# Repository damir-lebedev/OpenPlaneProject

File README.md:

<!-- download:start -->
<p align="center">

</p>
<p align="center"><a href="https://github.com/damir-lebedev/openplane-studio/releases/latest">OpenPlane Studio — настроить, прошить и полететь: самолёт и коптер (в том числе плату из-под Betaflight). Установщик работает без интернета — всё нужное внутри. На Android — настройка и прошивка в поле по кабелю USB-C ⇄ USB-C.</a></p>
<!-- download:end -->

<!-- i18n-bar:start -->
  <p align="center">
     <b>Читать на русском</b>
    &nbsp;·&nbsp;
    <a href="docs/i18n/en/README.md"> Read this in English</a>
    &nbsp;·&nbsp;
    <a href="docs/i18n/zh-CN/README.md"> 阅读中文版</a>
    &nbsp;·&nbsp;
    <a href="docs/i18n/es/README.md"> Lee esto en español</a>
  </p>
  <p align="center">
    <a href="docs/i18n/hi/README.md"> हिन्दी में पढ़ें</a>
    &nbsp;·&nbsp;
    <a href="docs/i18n/ar/README.md"> اقرأ بالعربية</a>
    &nbsp;·&nbsp;
    <a href="docs/i18n/pt-BR/README.md"> Leia em português</a>
    &nbsp;·&nbsp;
    <a href="docs/i18n/fr/README.md"> Lire en français</a>
  </p>
  <p align="center">
    <a href="docs/i18n/de/README.md"> Auf Deutsch lesen</a>
    &nbsp;·&nbsp;
    <a href="docs/i18n/ja/README.md"> 日本語で読む</a>
    &nbsp;·&nbsp;
    <a href="docs/i18n/ko/README.md"> 한국어로 읽기</a>
    &nbsp;·&nbsp;
    <a href="docs/i18n/sv/README.md"> Läs på svenska</a>
  </p>
<!-- i18n-bar:end -->

<p align="center">

  <br>

</p>

<h3 align="center">Выключили пульт — самолёт сам вернулся домой и кружит над вами.</h3>
<p align="center">Это не мультфильм: <b>вся прошивка</b> ведёт модель самолёта в замкнутом контуре — те же байты iBUS на входе, тот же ШИМ на выходе.</p>

---

## ⚡ За 30 секунд

| | |
|---|---|
| **Что это** | Открытый полётный контроллер и автопилот для радиоуправляемых самолётов. Основная плата — STM32H743 (класс плат Pixhawk): на плате DevEBox прошивка **уже запущена и управляется с пульта** — [есть видео](#-stm32h743-ожила-на-плате), сейчас подключаются датчики. Прежняя основа — ESP32-S3 за ~$10, на ней пройден стенд со всеми датчиками. |
| **Что умеет** | 12 режимов полёта — от стабилизации до возврата домой, кругов по GPS, запуска с руки, автопосадки и **парения в термиках**. Трубка Пито из двух дешёвых барометров. Телеметрия MAVLink в QGroundControl и Mission Planner. |
| **Мультикоптеры** | Та же прошивка — для квадро, гексы, окты, Y6 и X8: описываете раму, винты, моторы и батарею, а PID и фильтры прошивка выводит сама по физической модели. Пока проверено в симуляторе — [COPTER.md](docs/COPTER.md). Вся прошивка коптера летает и на ПК (SITL, `pio run -e sitl`) — в OpenPlane Studio это раздел «Симулятор» с 3D и управлением с пульта. |
| **Прошить** | Из [OpenPlane Studio](https://github.com/damir-lebedev/openplane-studio) одной кнопкой — Windows и macOS. Плата узнаётся сама, настройки коптера не стираются. **Studio для Android** — кабель USB-C ⇄ USB-C, вся настройка в поле и прошивка готовым файлом из релиза одной кнопкой «Скачать и прошить». |
| **Главная фишка** | Любой тумблер или крутилка пульта = любая функция. **Одна строка** в `Controls.h` — и SwD уже не реверс мотора, а сброс груза. |
| **Почему можно верить** | 710 автотестов (плюс 9 на самой плате с настоящей SD-картой), 94 % кода под тестами, 33 сборки «плата × датчики» без единого предупреждения, замкнутые симуляции каждого режима. |
| **Честно** | В воздухе пока был ручной режим (первый прототип). STM32H743 пока проверена на столе, без датчиков. Автопилот проверен на стенде, тестами и симуляциями и ждёт лётных испытаний — [статус ниже](#-честный-статус). |

---

## 🎛️ Тумблер = функция. Одна строка.

```cpp
// include/config/Controls.h
constexpr Binding BINDINGS[] = {
    Bind::modes  (Channels::SWC, MODE_MANUAL, MODE_STABILIZE, MODE_AUTO_TAKEOFF),
    Bind::feature(Channels::SWB, Feature::FLAPS),
    Bind::feature(Channels::SWD, Feature::MOTOR_REVERSE),// реверс мотора — только в DISARM
    Bind::knob   (Channels::VRA, Knob::STAB_GAIN),       // "мягче / жёстче" прямо в полёте
    Bind::knob   (Channels::VRB, Knob::CRUISE_SPEED),
};
```

Хотите на SwD парение в термиках вместо реверса? `Bind::mode(Channels::SWD, MODE_SOARING)`. Сброс груза на SwB? `Bind::feature(Channels::SWB, Feature::PAYLOAD_DROP)`. Ошиблись — например, повесили два режима на один тумблер или заняли стик — **сборка не пройдёт**: таблицу проверяет компилятор (`static_assert`). При включении борт сам печатает, что на каком тумблере.

**12 режимов · 11 функций · 8 крутилок** — всё с примерами в [справочнике автопилота](docs/AUTOPILOT_GUIDE.md).

---

## ✈️ Что умеет автопилот

| | Режим | Суть |
|---|---|---|
| 🕹️ | **MANUAL** | рули = стики, как без полётника |
| 🧭 | **STABILIZE** | стик задаёт угол; отпустил — самолёт сам в горизонте |
| 📏 | **ALT_HOLD** | + держит высоту по барометру |
| 🌀 | **ACRO** | стик задаёт скорость вращения — для фигур |
| 🛣️ | **CRUISE** | курс, высота и скорость держатся сами; стики только поправляют |
| ⭕ | **LOITER** | круги над точкой по GPS (радиус — крутилкой) |
| 🏠 | **RTH** | домой на 40 м и круги над головой; сам включается при потере связи |
| 🛫 | **AUTO_TAKEOFF** | взлёт с полосы: хвостовое или носовое колесо, хвост вверх, отрывает крыло |
| 🤾 | **LAUNCH** | запуск с руки: мотор после броска, набор высоты |
| 🛬 | **AUTO_LAND** | планирование и выравнивание у земли |
| 🦅 | **SOARING** | мотор выключен, находит термики и кружит в них |
| 🆘 | **RESCUE** | «спасите»: крылья ровно, нос вверх — из любой спирали |

Плюс: калибровка самолёта на земле с пульта (горизонт и стояночный угол, этапы — сигналами мотора и рулей), геозабор, автотриммер «кривого» самолёта, координация разворота, защита от сваливания по трубке Пито, закрылки и воздушный тормоз, сброс груза, стабилизированная камера, пищалка «ищите меня в траве».

---

## 📈 Каждый режим летает — в замкнутом контуре

Не «функция вернула число», а **полёт**: пульт → кадр iBUS → прошивка → ШИМ → отклонения рулей → модель самолёта с подъёмной силой, сваливанием, ветром и термиками → датчики → снова прошивка. 17 таких полётов — часть обычных тестов (`pio test -e native`).

<table>
  <tr>
    <td width="50%"></td>
    <td width="50%"></td>
  </tr>
  <tr>
    <td>🦅 Нашёл термик сам и набрал высоту <b>с выключенным мотором</b> — вариометр полной энергии не путает «ручку на себя» с восходящим потоком.</td>
    <td>🆘 Крен 60° — и через секунды горизонт. RESCUE вытаскивает из спирали с креном 70° и носом −40°.</td>
  </tr>
  <tr>
    <td></td>
    <td></td>
  </tr>
  <tr>
    <td>🤾 Бросок с руки → мотор только после того, как рука ушла от винта → набор. 🛬 Посадка: планирование и выравнивание на 3 м.</td>
    <td>🌬️ Скорость по трубке из двух <b>шумных</b> барометров со сдвигом 150 Па между чипами — ошибка меньше 0.5 м/с.</td>
  </tr>
</table>

---

## 🚁 Мультикоптеры: описал коптер — настройка готова

Квадро, гекса, окта, Y6, X8 — на тех же платах. **PID, фильтры, холостые и расходы руками не подбираются**: в `CopterConfig.h` — рама, винт, мотор, батарея и масса (или готовая сборка из каталога: от вупа 65 мм до гексы с винтами 15"), остальное прошивка выводит сама по модели мотора и винта — с запасом, который держит коптер, у которого тяга и инерция вдвое «не те». В полёте сама учит газ висения и ведёт режекторы за оборотами моторов.

| | |
|---|---|
| **Режимы** | ACRO (airmode), HORIZON, ANGLE, ALT_HOLD; на тумблерах — таблица `aux` как в Betaflight (по умолчанию ARM — SwA, режим — SwC), порядок каналов — `map` |
| **Настройки как в Betaflight** | CLI: `set`/`get`/`diff`/`save`, 4 PID-профиля и 4 профиля расходов, PID в единицах BF, diff из BF вставляется целиком (железо BF — пропускается, в конце — сводка); **конфигуратор Betaflight подключается по MSP** (коптер представляется как BF 4.5); описание коптера — тоже настройки; протокол `@params`/`@set` для приложения |
| **Защиты** | ARM только при всех проверках (каждая причина отказа — кодом, как в `status` BF, и словами), потеря связи → горизонт, снижение и DISARM на земле, переворот и отказ мотора → моторы стоп |
| **Регуляторы** | PWM, OneShot125/42, Multishot, DShot150/300/600 (таймер с DMA, до 8 моторов; на железе ещё не проверен); двунаправленный DShot — кадры и расшифровка оборотов готовы, чтение ответа — на стенде |
| **Полётники** | Matek H743, DevEBox H743 и **почти любой F405 из-под Betaflight** (ICM-42688-P, SPL06/DPS310): распиновку `tools/bf_board.py` снимает с самой платы — даже если её таргета нет ни в одном репозитории; родная прошивка сохраняется по DFU; первый F405 (GETFUN F405V3) прошёл стол — датчики, флеш, OSD, моторы |
| **FPV** | видеопередатчик по SmartAudio/Tramp с **потолком мощности** и уровнем с тумблера, OSD — чип AT7456E или цифровые очки DJI / Walksnail / HDZero (MSP DisplayPort): батарея, ток, мА·ч, время, дом, предупреждения; телеметрия в пульт по CRSF; GPS, компас и точка дома, **удержание высоты и позиции** (ALT HOLD, POS HOLD как в BF 2025: ветер 5 м/с — уход 0.3 м в симуляции); Li-ion с его порогами; PINIO (камеры, 12 В); пищалка |
| **Проверено** | 12 сборок × 3 варианта «не той» физики в симуляторе с 6 степенями свободы: висение ±0.3 м, наклон по стику за 0.14–0.35 с, посадка при потере связи. **В воздухе — ещё нет** |

```bash
pio run -e matek-h743-quad -t upload    # потом в консоли: t — настройка, m — моторы (без пропеллеров!)
```

Подробно — [COPTER.md](docs/COPTER.md).

### 🧱 Геозабор: дрон, который не улетит

Рисуете круг вокруг себя и потолок — и всё. **В любом режиме, даже в ACRO на полной скорости**, коптер к краю сам тормозит, а у края автомат перехватывает управление и ведёт назад — стики не слушаются. Пропал GPS — не ждёт: летит домой по своим датчикам или садится. В очках — радар: где край, где дом и сколько метров осталось.

<table>
  <tr>
    <td width="66%"></td>
    <td width="34%"></td>
  </tr>
  <tr>
    <td>OpenPlane Studio → «Безопасность»: Двор / Площадка / Поле, радиус, потолок, что делать без GPS. Справа от круга — радар, как его видно в очках.</td>
    <td><b>Настоящая траектория</b> из теста прошивки: робот-пилот минуту рвётся наружу, автомат перехватывает его 9 раз.</td>
  </tr>
</table>

### 🎮 Симулятор: полетай раньше, чем купишь

Это не игра с похожей физикой — это **та же прошивка**, что пойдёт в коптер (те же PID, фильтры, режимы и защиты), собранная для компьютера (`pio run -e sitl`); вместо датчиков — модель полёта. Стики — пульт по USB, геймпад или клавиатура; камера сзади, FPV или с земли; ворота для тренировки; упал — `R`, и снова на старте. Вкладка «Симулятор» в OpenPlane Studio — бесплатно.

---

## 🌬️ Трубка Пито за копейки

Нормальный датчик воздушной скорости стоит как половина полётника. Здесь — **два барометра**: BMP581 в трубке (полное давление) и основной барометр в фюзеляже (статика). Прошивка сама обнуляет разницу чипов на земле, фильтрует, считает плотность воздуха по высоте и температуре и замечает перепутанные шланги. Что это даёт: CRUISE держит **воздушную** скорость, а не газ; защита от сваливания; честная скорость в телеметрии. Сборка — в [справочнике](docs/AUTOPILOT_GUIDE.md#трубка-пито-своими-руками).

---

## 📡 Наземная станция: браузер или QGroundControl

<table>
  <tr>
    <td width="46%"></td>
    <td>
      <b>ESP32 — веб-дашборд прямо с борта.</b> Точка доступа <code>OpenPlane-Debug</code>, адрес <code>192.168.4.1</code>: каналы пульта, выходы, все датчики, режим, навигация, смена режима и ПИД на лету. Без приложений и лишнего железа.<br><br>
      <b>STM32H743 — MAVLink по радиомодему.</b> QGroundControl и Mission Planner видят борт как самолёт ArduPilot: горизонт, карта с домом, скорость по трубке, режимы именами ArduPlane, ПИД из окна параметров, смена режима кнопкой. ARM с земли — нельзя, только тумблером: так безопаснее.<br><br>
      Кадры MAVLink побайтно сверены с эталонной <code>pymavlink</code>.
    </td>
  </tr>
</table>

---

## 📼 Чёрный ящик

Плата пишет каждый полёт: IMU на 500 Гц, углы и решения автопилота, ПИД, все выходы, стики, барометр, компас, GPS, батарея и события — с ARM и газа до посадки, с 10 секундами до старта. **ESP32-S3** — во встроенный флеш (11.9 МБ, около 9 минут), **STM32H743** — на SD-карту (64 МБ — около часа; карта остаётся обычной FAT32, прошивка пишет в заранее созданный файл `BLACKBOX.BIN`). Стирание — только на земле. После полёта `python tools/blackbox.py download` скачивает полёт по USB и раскладывает в CSV; с SD-карты полёты разбираются и без платы: `python tools/blackbox.py ring E:/BLACKBOX.BIN`. Коптер пишет гироскоп, PID и моторы каждый цикл (1 кГц): на H743 — на ту же SD-карту, на F405 — на SPI-флеш платы (W25Q128 и т. п.); `python tools/blackbox.py download --bfl` отдаёт полёт коптера в формате Betaflight (`.BFL`) — для Blackbox Explorer и PIDtoolbox. Смотреть — в **OpenPlane Studio, раздел «Ящик»**: таймлайн с режимами и событиями, графики с общим курсором, спектр шума, ориентация в 3D. Подробно — [BLACKBOX.md](docs/BLACKBOX.md).

---

## 🔩 Железо: одна прошивка — пять плат, тринадцать датчиков

| Плата | Статус | Что проверено |
|---|---|---|
| **STM32H743VIT6** | ✅ основная · 🔧 DevEBox, датчики подключаются + 🧪 тесты | на плате: загрузка, консоль по USB, **SD-карта и чёрный ящик** (тесты на плате), **приём iBUS, ARM и управление сервами и мотором с пульта** (запуск на видео); на ПК — вся прошивка: задачи FreeRTOS, флеш, MAVLink, I2C и SPI. **LSM6DSV на второй шине I2C** (PB9/PB8) — найден сам, гироскоп и акселерометр живые; компас QMC6309 за LSM6DSV — через sensor hub, работает |
| **Matek H743-WING V3** | 🧪 тесты · готовый полётник | вся прошивка на ПК с датчиками платы (ICM-42688-P, DPS310), внешней шиной I2C и калибровкой установки IMU; на настоящей плате ещё не проверяли |
| **ESP32-S3 N16R8** | ✅ прежняя основная, на стенде | все датчики, сервы, iBUS, OLED, дашборд вживую; прошивка целиком — в тестах |
| **ESP32 38-pin** | 🧪 тесты | прошивка целиком в тестах с набором ICM-45686 |
| **ESP32-C3 SuperMini** | ✈️ летал (ручной) | первый прототип; сборка всех наборов |

| Датчик | Что это | Шины |
|---|---|---|
| **LSM6DSV** + **QMC6309** | IMU + компас (модуль) | I2C / SPI |
| **ICM-45686** + **QMC6309** | IMU + компас (замена) | I2C / SPI |
| **SPL06-001** | барометр фюзеляжа | I2C / SPI |
| **DPS310** | барометр на плате Matek H743 | I2C |
| **BMP581** | основной барометр и барометр в трубке Пито | I2C / SPI |
| MPU6050/6500, ICM-42688, BMP388, BME280, QMC5883P/L | стендовые и прежние | I2C / SPI |
| **u-blox M10** | GPS, 10 Гц, UBX | UART |
| **iBUS · SBUS · CRSF** | приёмник пульта: FlySky, FrSky, Futaba, RadioMaster, ExpressLRS, TBS Crossfire | UART |

Датчик меняется одной строкой (`SENSOR_KIT_LSM6DSV_PITOT`), плата — одним флагом сборки. Все 4 платы × 7 наборов датчиков и Matek H743 со своим набором собираются без предупреждений: [`tools/build_matrix.sh`](tools/build_matrix.sh).

<table>
  <tr>
    <td width="50%"></td>
    <td width="50%"></td>
  </tr>
  <tr>
    <td>Стенд на ESP32-S3: IMU, барометр, компас, OLED, сервы, приёмник.</td>
    <td>Тест винтомоторной группы.</td>
  </tr>
</table>

### 🎥 STM32H743 ожила на плате

Прошивка для STM32H743 запущена на плате DevEBox **без единого датчика** и управляется с обычного пульта: приёмник по iBUS, ARM, сервы и мотор отвечают на стики и тумблеры в ручном режиме. Весь запуск снят на видео.

▶️ **[Смотреть запуск на видео](https://t.me/lisnmylife/420)**

Что это доказывает: тракт «пульт → iBUS → прошивка → ШИМ» работает на настоящем железе, а не только в тестах. Что ещё не доказано: датчики (IMU, барометр, GPS) к этой плате не подключали, поэтому режимы автопилота на ней пока не пробовались.

---

## 🧪 Качество, которое можно проверить

| | |
|---|---|
| **710 автотестов** | модули, драйверы по регистрам чипов, замкнутые полёты, прошивка ESP32 и STM32 **целиком** на ПК; плюс 9 тестов на самой плате STM32 с настоящей SD-картой |
| **94.1 % строк, 85.2 % ветвлений** | покрытие `gcovr`, включая код STM32 |
| **33/33 сборки** | 4 платы × 7 наборов датчиков + Matek H743, `-Wall -Wextra`, ноль предупреждений; плюс 2 сборки коптера |
| **0 замечаний** | cppcheck и clang-tidy по всему коду |
| **Эталоны, а не копии кода** | формулы датчиков — по датащитам (Bosch, ST, TDK, Goertek), MAVLink — по pymavlink |

```bash
pio test -e native -e native-stm32   # все тесты, ~1.5 минуты, железо не нужно
```

Подробно — [TESTING.md](docs/TESTING.md).

---

## 🧠 Как устроено

```mermaid
flowchart LR
    RC["Пульт FS-i6<br/>iBUS"] --> SW["PilotSwitches<br/>Controls.h"]
    SENS["IMU · барометры · компас<br/>GPS · трубка Пито"] --> AP
    SW --> AP["Autopilot<br/>12 режимов · навигация<br/>failsafe · геозабор"]
    AP --> FC["FlightController<br/>ARM · микшер · закрылки"]
    FC --> OUT["Сервы · ESC<br/>груз · камера"]
    AP -.-> TLM["Дашборд Wi-Fi<br/>MAVLink · OLED"]
```

- **Header-only C++**, одна единица трансляции, никакой динамической памяти в полётном контуре. Любитель `.h/.cpp`? Для вас — параллельная ветка [`feature/split-headers`](https://github.com/damir-lebedev/OpenPlaneProject/tree/feature/split-headers): генерируется из этой скриптом, прошивка с LTO того же размера.
- **HAL** — единственный слой, знающий MCU: новая плата — это новый `Board`, а не переписанный автопилот.
- **Драйвер датчика не знает шину**: один класс работает по I2C и по SPI.
- **Безопасность — порядком операций**: потеря связи > ARM > режим > газ; ни один режим не протащит газ мимо ARM.

Подробно — [ARCHITECTURE.md](docs/ARCHITECTURE.md).

---

## 🚀 Быстрый старт

Проще всего — **[OpenPlane Studio](https://github.com/damir-lebedev/openplane-studio)** ([скачать](https://github.com/damir-lebedev/openplane-studio/releases/latest)): приложение для Windows и macOS (и Android — настройка и прошивка готовым файлом) настраивает плату под ваш самолёт по шагам, собирает прошивку и прошивает её одной кнопкой, а потом помогает наладить всё на земле по живым данным с платы. Из командной строки:

```bash
pip install platformio
git clone https://github.com/damir-lebedev/OpenPlaneProject && cd OpenPlaneProject
pio run -e stm32h743-devebox -t upload                    # DevEBox H743: USB DFU, консоль по USB
pio run -e matek-h743 -t upload                           # Matek H743-WING V3: кнопка BOOT + USB
pio run -e esp32-s3 -t upload && pio device monitor     # ESP32-S3
pio run -e stm32h743 -t upload                            # STM32H743 (ST-Link)
pio run -e matek-h743-quad -t upload                      # мультикоптер на Matek H743 (docs/COPTER.md)
```

DevEBox: на плате нет кнопки BOOT0 — перед первой заливкой соедините пин BT0 с 3V3 и нажмите RST; потом клавиша `D` в консоли сама перезагружает плату в загрузчик ([подробно](docs/DEVELOPER_GUIDE.md#stm32h743)).

В мониторе порта: `h` — меню, `b` — какие чипы видны на шинах, `s` — датчики, `p` — проверка выходов (пропеллер снять!). Дальше — [гайд пилота](docs/PILOT_GUIDE.md).

---

## 🟢 Честный статус

| Что | Где проверено |
|---|---|
| Ручное управление, микшер | ✈️ в полёте (первый прототип, C3) |
| ARM, failsafe, закрылки, сервы, мотор | 🔧 на стенде (S3) |
| Двунаправленный ESC BLHeli 80A, реверс только в DISARM | 🧪 тесты; с регулятором ещё не проверяли |
| Автовзлёт с хвостовым и носовым колесом, калибровка на земле с пульта, сигналы мотором и рулями | 🧪 тесты и симуляции с моделью шасси; мелодию ESC после паузы импульсов — проверить на стенде |
| STABILIZE | 🔧 на стенде: рули отвечают на наклоны в правильную сторону |
| Датчики стенда (MPU6500, BMP388, QMC5883P), OLED, дашборд | 🔧 на стенде |
| Остальные режимы, навигация, трубка Пито, MAVLink | 🧪 тесты и замкнутые симуляции |
| Новые датчики (LSM6DSV, ICM-45686, QMC6309, SPL06, BMP581) | 🧪 регистровые эмуляторы по датащитам |
| STM32H743: SD-карта, чёрный ящик, консоль по USB | 🔧 на плате DevEBox (тесты на плате) |
| STM32H743: iBUS, ARM, ШИМ на серво и мотор, ручное управление | 🔧 на плате без датчиков, снято на видео |
| Приёмники SBUS и CRSF (ExpressLRS) | 🧪 тесты: разбор кадров, failsafe, UART с инверсией; с настоящим приёмником ещё не проверяли |
| Matek H743-WING V3: датчики на плате, внешняя шина I2C, калибровка установки IMU | 🧪 вся прошивка на ПК; на настоящей плате ещё не проверяли |
| STM32H743: датчики (IMU, барометр, компас, GPS) и режимы автопилота | 🧪 вся прошивка на ПК; к плате датчики ещё не подключали |
| Мультикоптеры: настройка из описания, режимы, failsafe, защиты | 🧪 симулятор с 6 степенями свободы (12 сборок × 3 физики) и вся прошивка на ПК; в воздухе ещё не было |

Модель самолёта в симуляциях упрощённая, коэффициенты — стартовые. Каждый новый режим сначала пробуется на высоте, с пальцем на тумблере MANUAL.

---

## 🗺️ Дорожная карта

- [x] Ручное управление, ARM, failsafe, объектная прошивка, веб-дашборд
- [x] Стенд ESP32-S3 со всеми датчиками — вживую
- [x] 12 режимов, навигация по GPS, RTH при потере связи, геозабор
- [x] Тумблеры и крутилки одной строкой, сброс груза, камера, автотриммер
- [x] Трубка Пито из двух барометров, защита от сваливания
- [x] Новые датчики: LSM6DSV, ICM-45686, QMC6309, SPL06, BMP581
- [x] STM32H743: полная прошивка, MAVLink, настройки во флеше
- [x] Замкнутые симуляции всех режимов, прошивка целиком в тестах
- [x] Чёрный ящик: полёт во флеш (ESP32-S3) и на SD-карту (STM32H743), выгрузка и разбор в CSV
- [x] STM32H743 запущена на плате: пульт → iBUS → сервы и мотор (без датчиков, на видео)
- [x] Приложение [OpenPlane Studio](https://github.com/damir-lebedev/openplane-studio): настройка по шагам, прошивка одной кнопкой, наладка на земле
- [x] Приёмники SBUS и CRSF (ExpressLRS, TBS Crossfire) рядом с iBUS — выбор в `Config.h` или в OpenPlane Studio
- [x] Готовый полётник Matek H743-WING V3: датчики на плате, прошивка одной кнопкой (на железе ещё не проверяли)
- [x] Мультикоптеры (квадро, гекса, окта, Y6, X8): настройка из описания коптера, проверено в симуляторе
- [x] Коптер в OpenPlane Studio: в ангаре рядом с самолётами, прошивка одной кнопкой, первая настройка (приёмник, видео с потолком мощности, тумблеры)
- [x] Коптер в OpenPlane Studio как в конфигураторе Betaflight: вкладки PID, расходы, приёмник, режимы, моторы (проверка ползунками), питание, видео, CLI; переход с Betaflight одной кнопкой — распиновка и родная прошивка снимаются с платы сами
- [x] Датчики на любой шине I2C (прошивка ищет сама), несколько чипов одного типа (основной + запасные), плавный спад газа на ESC
- [ ] STM32H743: подключить датчики и пройти стенд так же, как ESP32-S3
- [x] Коптер: чёрный ящик на SD-карту и его просмотр в OpenPlane Studio
- [x] Коптер: настройки как в Betaflight (CLI, diff из BF, MSP для конфигуратора BF), батарея и failsafe как в BF, DShot на таймере с DMA, ящик на SPI-флеше F405, журнал в формате Betaflight
- [ ] Коптер: DShot и двунаправленный DShot на стенде, цикл 4 кГц, MAVLink, лётные испытания
- [ ] Популярные полётники на STM32F405: SpeedyBee F405 WING, Matek F405-WTE
- [ ] Лётные испытания автопилота на новом планере
- [ ] Своя плата полётника на STM32H743: носитель под DevEBox разведён ([FC_BOARD_H743.md](docs/FC_BOARD_H743.md), файлы для EasyEDA/KiCad и лазера — [hardware/fc-carrier-h743/](hardware/fc-carrier-h743/))
- [ ] Полёт по маршрутным точкам, миссии MAVLink
- [ ] Адаптивная обратная связь (заготовка уже проверена в симуляции)
- [ ] Датчик тока и батареи, телеметрия на пульт (iBUS-SENS)
- [ ] Автономная доставка: маршрут → сброс груза → домой

Подробно — [ROADMAP.md](docs/ROADMAP.md).

---

## 💼 Для партнёров и инвесторов

Небольшие самолёты-доставщики и мониторинговые борта — это либо закрытые дорогие платформы, либо разрозненные хобби-проекты. OpenPlane целится в середину: **открытый, проверяемый автопилот на массовом железе**, где каждая функция покрыта тестами и может быть адаптирована под задачу — доставка медикаментов в труднодоступные места, мониторинг полей и лесов, поисковые работы.

Что уже сделано на свои: архитектура, которая переносится между платами без переписывания; автопилот с полным набором режимов; инфраструктура тестов, на которой новые функции появляются быстро и не ломают старые. Что ускорят ресурсы: лётные испытания, своя плата полётника на STM32H743, полёт по маршруту и сброс груза. Куда и зачем — [ROADMAP.md](docs/ROADMAP.md).

---

## 📚 Документация

| Документ | Для кого |
|---|---|
| [COPTER.md](docs/COPTER.md) | мультикоптеры: каталог сборок, свой коптер, первый запуск, режимы, защиты, как проверено |
| [AUTOPILOT_GUIDE.md](docs/AUTOPILOT_GUIDE.md) | пилоту: каждый режим, функция и крутилка, как повесить на тумблер, трубка Пито, наземная станция |
| [PILOT_GUIDE.md](docs/PILOT_GUIDE.md) | сборка, распиновка, пульт, failsafe, первый полёт |
| [DEVELOPER_GUIDE.md](docs/DEVELOPER_GUIDE.md) | разработчику: файлы, знаки, API, как добавить датчик, режим, плату |
| [ARCHITECTURE.md](docs/ARCHITECTURE.md) | слои, задачи, такт управления, автоматы |
| [TESTING.md](docs/TESTING.md) | тесты, симуляции, покрытие, анализ |
| [reference/](docs/reference/README.md) | справочник по каждому классу |
| [FC_BOARD_H743.md](docs/FC_BOARD_H743.md) · [FC_BOARD.md](docs/FC_BOARD.md) · [ROADMAP.md](docs/ROADMAP.md) | носитель под DevEBox H743 · прежняя плата под ESP32-S3 · куда движется проект |
| [hardware/fc-carrier-h743/](hardware/fc-carrier-h743/) | плата-носитель под DevEBox H743: KiCad/EasyEDA, рисунок меди для лазера, генератор |
| [airframe/](airframe/README.md) | планер Astro-Cargo: проект Fusion 360 и STL для печати, известные недостатки версии v2 |

> **Приложение:** [OpenPlane Studio](https://github.com/damir-lebedev/openplane-studio) — настройка платы по шагам, сборка и прошивка одной кнопкой, наладка на земле по живым данным; интерфейс на русском и английском.

> **Связанный проект:** [esp32-rc-joystick](https://github.com/damir-lebedev/esp32-rc-joystick) — пульт FS-i6 как USB-джойстик для симулятора на той же ESP32-S3: сначала налетать часы в симуляторе, потом — в поле.

---

## 🤝 Участие

Нужны руки и головы: аэродинамика и авиамоделизм, 3D-печать и прочность, встраиваемый C++, датчики и автопилоты, наземные интерфейсы. Issues и pull request'ы — в ветку `main`; начать — с [DEVELOPER_GUIDE.md](docs/DEVELOPER_GUIDE.md).

## 📜 Лицензия

[OpenPlane License 2.0](LICENSE) — проект открыт и общедоступен: код, документацию, схемы и модель планера можно читать, копировать, менять и выкладывать свои доработки **бесплатно для некоммерческого использования**. Зарабатывать на проекте можно только по платной лицензии от автора.

**Бесплатно и без спроса:** личное и хобби-использование — собрать, доработать, летать; свои доработки и форки, выложенные бесплатно под этой же лицензией; учёба и исследования в некоммерческих учебных и научных организациях, клубы и соревнования; некоммерческие организации, включая волонтёрский поиск и спасение; видео, стримы и статьи о проекте, даже с рекламой и донатами; продажа частным лицом своих б/у самолётов или плат, собранных для себя, — не больше двух в год.

**Только по платной лицензии:** продажа плат, полётников, наборов, готовых самолётов и любых изделий с этой прошивкой или по этим чертежам; платные услуги на её основе (доставка, съёмка, картография, обследования, сельское хозяйство, прошивка и настройка за деньги); использование в компании и в её продуктах; платные курсы. Связь с автором: dam.lebedev2018@yandex.ru, dam.lebedev2020@gmail.com, Telegram [t.me/lisnmylife](https://t.me/lisnmylife).

Для всех, включая коммерческих лицензиатов:

1. **Укажите автора — Damir Lebedev (Damn / Проклятый)** там, где его увидят пользователи вашего результата, например: «Based on OpenPlane by Damir Lebedev». Текст лицензии оставляйте вместе с кодом; изменённую версию нельзя выдавать за оригинал.
2. **Военное применение — только по письменному договору государства с автором**, подписанному до начала применения. Негосударственным группам, частным компаниям и частным лицам без такого договора с государством военное применение запрещено.
3. **Нельзя намеренно вредить людям и имуществу без их предварительного письменного согласия**, если договор по пункту 2 прямо не говорит иное. Свою технику ломать можно, если это никому не угрожает.
4. **Соблюдайте технику безопасности и законы** при сборке, испытаниях и полётах.

Присылая pull request, вы разрешаете автору распространять ваш вклад на любых условиях, включая коммерческие лицензии; авторские права на вклад остаются за вами. Если условия нарушены, разрешение на использование прекращается. Это лицензия source-available, а не open source в понимании OSI. Редакция 2.0 действует для всех версий, опубликованных с 3 ноября 2026 года.

Юридическую силу имеет только английский текст в файле [LICENSE](LICENSE): переводы лицензии на другие языки даны для удобства.

Прошивка управляет летательным аппаратом и не сертифицирована. Всё, что вы с ней делаете, — на ваш страх и риск; автор ответственности не несёт.

```text
OpenPlane © 2026 Damir Lebedev (Damn / Проклятый) — https://github.com/damir-lebedev/OpenPlaneProject
```

<p align="center"><i>Первый прототип сломался в первом же полёте — поэтому здесь всё на виду: код, тесты, проблемы. Собирайте, ломайте, чините вместе с нами.</i></p>

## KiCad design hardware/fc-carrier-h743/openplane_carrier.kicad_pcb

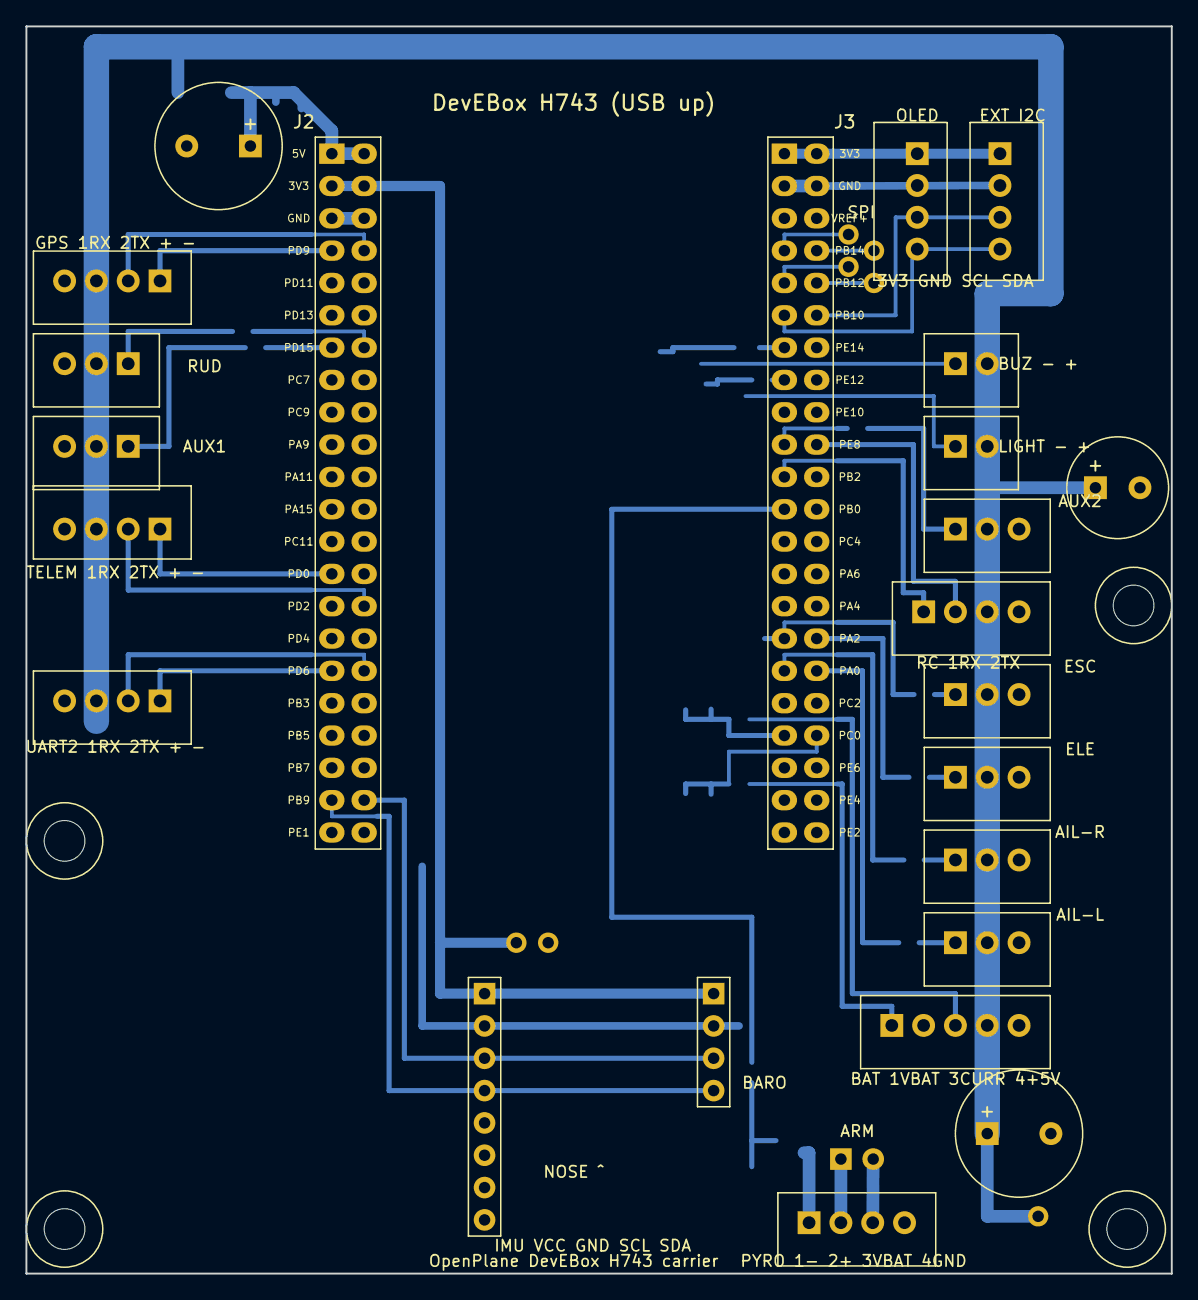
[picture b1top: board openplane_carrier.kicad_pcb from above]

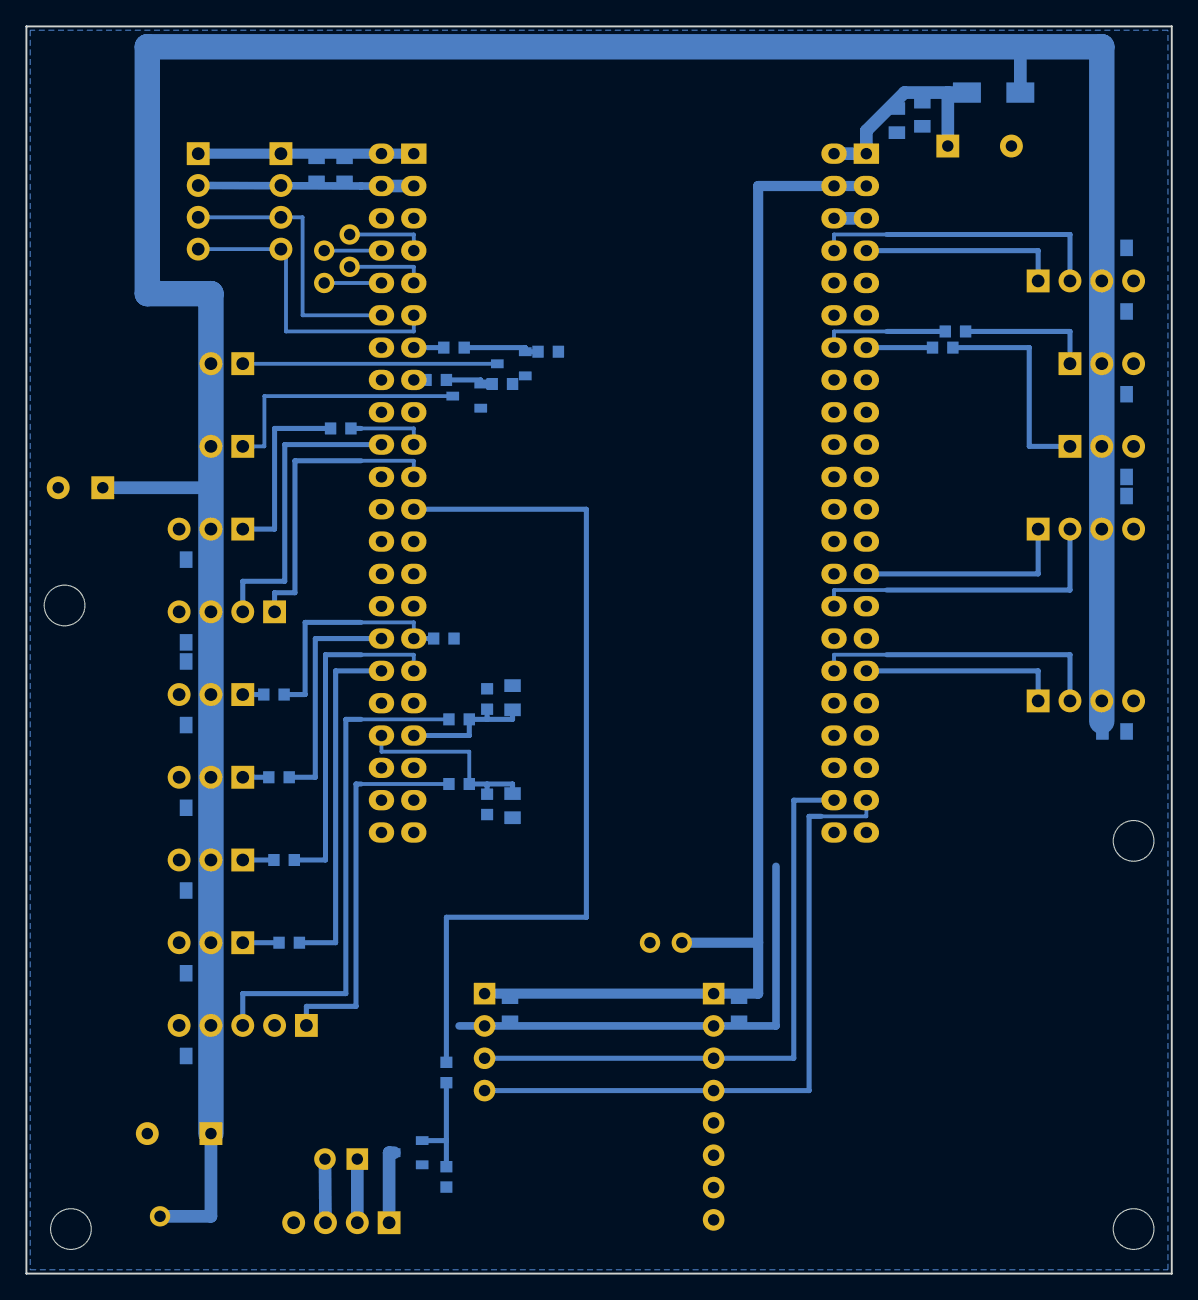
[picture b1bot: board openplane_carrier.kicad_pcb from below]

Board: 2 copper layers, 90.0 x 98.0 mm, 80 parts (44 on the bottom side), 50 nets.

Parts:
ARM: Jumper_2.54
B1: JST_XH_5
BARO: PinSocket_1x4
BUZ: JST_XH_2
C1, C3, C7: C_0805_10u
C2, C4, C5, C6, C8: C_0805_100n
CE1: CP_Radial_D8
CE2, CE3: CP_Radial_D10
CL0, CL1, CL2, CL3, CL4: C_0805_100n
CL_GPS10: C_0805_10u
CR2, CR3, CR4, CR5, CR6, CR7, CR8: C_0805_100n
CR_ESC10: C_0805_10u
D1: D_SMA_SS16
EXT: JST_XH_4
GPS: JST_XH_4
H1, H2, H3, H4: MountingHole_M3
IMU: PinSocket_1x8
J2, J3: Socket_2x22_DevEBox
LIGHT: JST_XH_2
OLED: JST_XH_4
PYRO: JST_XH_4
Q1, Q2, Q3: SOT-23_Si2302
R1, R3, R15: R_0603_100
R2, R4, R16: R_0603_100k
R5, R6, R7, R8, R9, R17, R18: R_0603_330
R10, R11, R14: R_0603_10k
R12: R_0603_15k
R13: R_0603_56k
RC: JST_XH_4
S1, S3, S4, S5, S6, S7, S8: JST_XH_3
TEL: JST_XH_4
TP_3V3, TP_5VB: TestPad_1.7
TP_CS: TestPad_1.7
TP_GND: TestPad_1.7
TP_MISO: TestPad_1.7
TP_MOSI: TestPad_1.7
TP_SCK: TestPad_1.7
UART2: JST_XH_4

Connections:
+3V3: C3.1, C4.1, EXT.1, J3.1, J3.2, OLED.1
+3V3B: BARO.1, C7.1, C8.1, IMU.1, J2.3, J2.4, TP_3V3.1
+5VB: B1.4, BUZ.2, CE1.1, CE2.1, CL0.2, CL1.2, CL2.2, CL3.2, CL4.2, CL_GPS10.2, CR2.1, CR3.1, CR4.1, CR5.1, CR6.1, CR7.1, CR8.1, CR_ESC10.1, D1.2, GPS.3, LIGHT.2, RC.3, S1.2, S3.2, S4.2, S5.2, S6.2, S7.2, S8.2, TEL.3, TP_5VB.1, UART2.3
+5VD: C1.1, C2.1, CE3.1, D1.1, J2.1, J2.2
AILL: J3.34, R9.1
AILL_O: R9.2, S6.1
AILR: J3.33, R8.1
AILR_O: R8.2, S5.1
AUX1: J2.13, R18.2
AUX1_O: R18.1, S8.1
AUX2: J3.19, R5.1
AUX2_O: R5.2, S1.1
BUZ_D: BUZ.1, Q1.3
BUZ_G: Q1.1, R1.1, R2.2
BUZ_IO: J3.13, R1.2
CS_IMU: J3.10, TP_CS.1
CURR_IN: B1.3, R11.2
CURR_S: C5.2, J3.37, R11.1, R12.2
ELE: J3.32, R7.1
ELE_O: R7.2, S4.1
ESC: J3.31, R6.1, R10.2
ESC_O: R6.2, S3.1
GND: B1.5, BARO.2, C1.2, C2.2, C3.2, C4.2, C5.1, C6.2, C7.2, C8.2, CE1.2, CE2.2, CE3.2, CL0.1, CL1.1, CL2.1, CL3.1, CL4.1, CL_GPS10.1, CR2.2, CR3.2, CR4.2, CR5.2, CR6.2, CR7.2, CR8.2, CR_ESC10.2, EXT.2, GPS.4, IMU.2, J2.5, J2.6, J3.3, J3.4, OLED.2, PYRO.4, Q1.2, Q2.2, Q3.2, R2.1, R4.1, R10.1, R12.1, R14.2, R16.2, RC.4, S1.3, S3.3, S4.3, S5.3, S6.3, S7.3, S8.3, TEL.4, TP_GND.1, UART2.4
GPS_RX: GPS.1, J2.7
GPS_TX: GPS.2, J2.8
LIGHT_D: LIGHT.1, Q2.3
LIGHT_G: Q2.1, R3.1, R4.2
LIGHT_IO: J3.15, R3.2
MISO: J3.8, TP_MISO.1
MOSI: J3.7, TP_MOSI.1
PYRO_D: PYRO.1, Q3.3
PYRO_G: Q3.1, R15.2, R16.1
PYRO_IO: J3.23, R15.1
PYRO_P: ARM.1, PYRO.2
RC_RX: J3.21, RC.1
RC_TX: J3.20, RC.2
RUD: J2.14, R17.2
RUD_O: R17.1, S7.1
SCK: J3.9, TP_SCK.1
SCL_A: EXT.3, J3.12, OLED.3
SCL_B: BARO.3, IMU.3, J2.42
SDA_A: EXT.4, J3.11, OLED.4
SDA_B: BARO.4, IMU.4, J2.41
TEL_RX: J2.27, TEL.1
TEL_TX: J2.30, TEL.2
U2_RX: J2.33, UART2.1
U2_TX: J2.34, UART2.2
VBAT_IN: B1.1, R13.2
VBAT_S: C6.1, J3.38, R13.1, R14.1
VPYRO: ARM.2, PYRO.3

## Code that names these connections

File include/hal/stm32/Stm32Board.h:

#pragma once
#include <Arduino.h>
#include <SPI.h>
#include <Wire.h>

#include "config/Config.h"
#include "hal/IBoard.h"
#include "hal/stm32/Stm32I2CBus.h"
#include "hal/stm32/Stm32ServoOutput.h"
#include "hal/stm32/Stm32SpiBus.h"
#include "hal/stm32/Stm32UartPort.h"

// ============================================================
// 🧠 РЕАЛИЗАЦИЯ "МОЗГА" ДЛЯ STM32H743 (STM32duino 3.x)
//
// Собирается полная прошивка (env stm32h743, src/stm32/main.cpp); на
// железе проверена голая плата DevEBox H743 (без датчиков и серв),
// шины, ШИМ и UART ещё ждут стенда — основная лётная плата ESP32-S3.
//
// Тот же публичный API, что у Esp32Board: единственное место, которое
// создаёт конкретные шины STM32 (TwoWire/SPIClass/Uart/HardwareTimer)
// и знает пины из Config.h (блок BOARD_STM32H743). Остальной код
// видит только IBoard.
//
// Отличия от ESP32, спрятанные здесь:
//   - периферию (I2C1/I2C2, SPI2, USART3, UART4, UART7, TIMx) ядро выбирает
//     само по номерам пинов — номеров контроллеров в Config.h нет;
//   - пины UART задаются при создании Uart, а не в begin();
//   - PWM — аппаратные таймеры, общие для выходов на одном TIMx
//     (см. Stm32ServoOutput.h).
// ============================================================

class Stm32Board : public IBoard
{
public:

    Stm32Board()
        : secondWire(pinOf(Config::PIN_I2C2_SDA), pinOf(Config::PIN_I2C2_SCL)),
          externalWire(pinOf(Config::PIN_I2C_EXT_SDA), pinOf(Config::PIN_I2C_EXT_SCL)),
          i2cBus(Wire, pinOf(Config::PIN_I2C_SDA), pinOf(Config::PIN_I2C_SCL), Config::I2C_CLOCK_KHZ * 1000UL),
          secondBus(secondWire, pinOf(Config::PIN_I2C2_SDA), pinOf(Config::PIN_I2C2_SCL), Config::I2C_CLOCK_KHZ * 1000UL),
          externalBus(externalWire, pinOf(Config::PIN_I2C_EXT_SDA), pinOf(Config::PIN_I2C_EXT_SCL), Config::I2C_CLOCK_KHZ * 1000UL),
          spiBus(SPI, pinOf(Config::PIN_SENSOR_SPI_SCK), pinOf(Config::PIN_SENSOR_SPI_MISO), pinOf(Config::PIN_SENSOR_SPI_MOSI)),
          rcPort(Config::PIN_RC_RX, Config::PIN_RC_TX),
          gpsPort(Config::PIN_GPS_RX, Config::PIN_GPS_TX),
          telemetryPort(Config::PIN_TELEM_RX, Config::PIN_TELEM_TX),
          servos{
              Stm32ServoOutput(Config::PIN_AILERON_LEFT),
              Stm32ServoOutput(Config::PIN_AILERON_RIGHT),
              Stm32ServoOutput(Config::PIN_ELEVATOR),
              Stm32ServoOutput(Config::PIN_ESC),
              Stm32ServoOutput(Config::PIN_RUDDER),
              Stm32ServoOutput(Config::PIN_AUX1),
              Stm32ServoOutput(Config::PIN_AUX2)
          }
    {
    }

    void begin() override
    {
        i2cBus.begin();
        spiBus.begin();
        if (hasSecondBus()) secondBus.begin();
        if (hasExternalBus()) externalBus.begin();

        pinMode(pinOf(Config::PIN_BUZZER), OUTPUT);
        digitalWrite(pinOf(Config::PIN_BUZZER), LOW);
    }

    II2CBus& i2c() override { return i2cBus; }
    ISpiBus& spi() override { return spiBus; }
    II2CBus* secondI2c() override { return hasSecondBus() ? &secondBus : nullptr; }
    II2CBus& externalI2c() override { return hasExternalBus() ? static_cast<II2CBus&>(externalBus) : i2cBus; }

    IUartPort& rcUart() override { return rcPort; }
    IUartPort& gpsUart() override { return gpsPort; }
    IUartPort* telemetryUart() override { return &telemetryPort; }

    // P63 (коптер): приёмник, GPS и MSP — на UART из настроек serial_*_uart;
    // пара ножек {rx, tx}, −1 −1 — роли нет. До begin() портов.
    void rebindUarts(const int16_t rc[2], const int16_t gps[2], const int16_t msp[2])
    {
        rcPort.rebind(rc[0], rc[1]);
        gpsPort.rebind(gps[0], gps[1]);
        telemetryPort.rebind(msp[0], msp[1]);
    }

    IServoOutput& servo(uint8_t channel) override { return servos[channel]; }

    void setBuzzer(bool on) override
    {
        digitalWrite(pinOf(Config::PIN_BUZZER), on ? HIGH : LOW);
    }


private:

    // Второй и третий контроллеры I2C — свои объекты TwoWire (глобальный
    // Wire занят шиной датчиков). Объявлены раньше шин, которые хранят
    // ссылки на них. Пин −1 — такой шины на плате нет: второй (Matek)
    // или отдельного внешнего разъёма (DevEBox).
    TwoWire secondWire;
    TwoWire externalWire;

    Stm32I2CBus i2cBus;
    Stm32I2CBus secondBus;
    Stm32I2CBus externalBus;
    Stm32SpiBus spiBus;

    Stm32UartPort rcPort;
    Stm32UartPort gpsPort;
    Stm32UartPort telemetryPort;   // самолёт: радиомодем MAVLink; коптер: MSP (очки)

    Stm32ServoOutput servos[ServoChannel::COUNT];

    static constexpr bool hasSecondBus() { return Config::PIN_I2C2_SDA >= 0 && Config::PIN_I2C2_SCL >= 0; }
    static constexpr bool hasExternalBus() { return Config::PIN_I2C_EXT_SDA >= 0 && Config::PIN_I2C_EXT_SCL >= 0; }

    // В Config.h пины — int16_t (−1 = не разведён); API ядра ждёт pin_size_t.
    static constexpr pin_size_t pinOf(int16_t pin)
    {
        return static_cast<pin_size_t>(pin);
    }
};

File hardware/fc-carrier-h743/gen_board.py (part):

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track("GPS_TX", WG, j2(8), (X2i, gp(3)), (X2o - 1.6, gp(3)))
track("GPS_TX", WS, (X2o - 1.6, gp(3)), (L2, gp(3)), (L2, YL["GPS"]))
track("GPS_RX", WS, j2(7), (L1, ry(4)), (L1, YL["GPS"]))
# RUD: PD14 (J2-14 внутр.) через 6/7 -> S7; AUX1: PD15 -> S8
track("RUD", WG, j2(14), (X2i, gp(6)), (X2o - 1.6, gp(6)))
r1, r2 = r0603("R17", "330", 17.0, gp(6), "RUD_O", "RUD")
track("RUD", WS, (X2o - 1.6, gp(6)), r2)
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track("SCL_B", WS, j2(42), (XSCL, ry(21)), (XSCL, YB[2]), (BARO_X, YB[2]))
track("SDA_B", WG, j2(41), (X2o, gp(21)), (X2i + 1.0, gp(21)))
track("SDA_B", WS, (X2i + 1.0, gp(21)), (XSDA, gp(21)), (XSDA, YB[3]), (BARO_X, YB[3]))
pinsocket("IMU", [(IMU_X, YB[0] + i * P) for i in range(8)], ["+3V3B", "GND", "SCL_B", "SDA_B", "", "", "", ""])
pinsocket("BARO", [(BARO_X, y) for y in YB], ["+3V3B", "GND", "SCL_B", "SDA_B"])
c1, c2 = c0805("C7", "10u", 34.0, 77.27, "+3V3B", "GND", vertical=True)
c1, c2 = c0805("C8", "100n", 52.0, 77.27, "+3V3B", "GND", vertical=True)

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

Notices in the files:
README.md:
License: OpenPlane License 2.0
